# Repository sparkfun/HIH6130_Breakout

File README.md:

HIH6130 Breakout - Humidity and Temperature Sensor
===================================================

[
*HIH6130 Breakout (SEN-11295)*](https://www.sparkfun.com/products/11295)

This is a breakout for the HIH6130 digital output-type relative humidity and temperature sensor.

Repository Contents
-------------------
* **/Hardware** - All Eagle design files (.brd, .sch, .STL)
* **/Production** - Test bed files and production panel files

License Information
-------------------
The hardware is released under [Creative Commons ShareAlike 4.0 International](https://creativecommons.org/licenses/by-sa/4.0/).

Distributed as-is; no warranty is given.

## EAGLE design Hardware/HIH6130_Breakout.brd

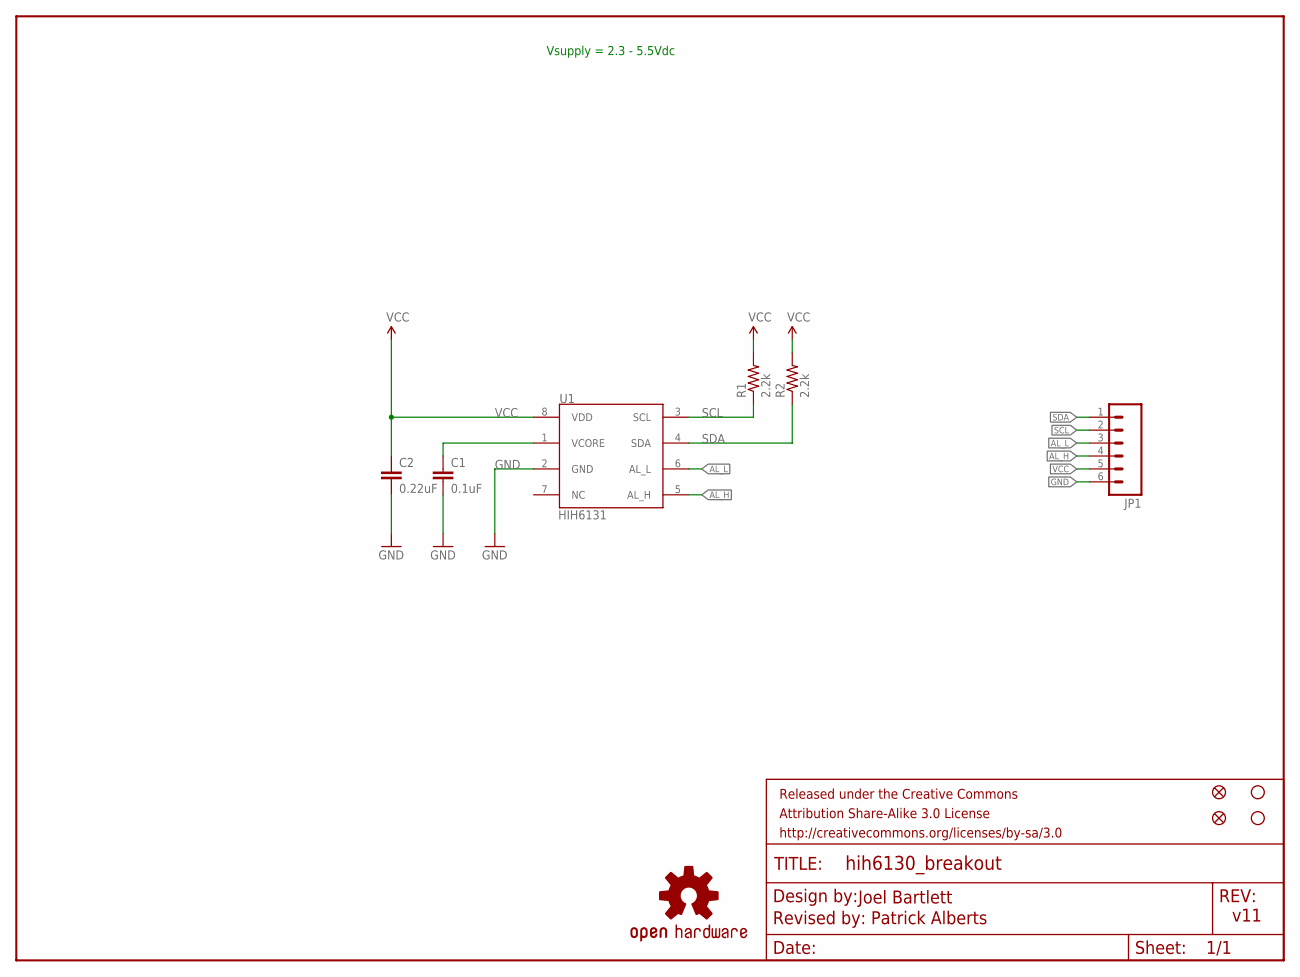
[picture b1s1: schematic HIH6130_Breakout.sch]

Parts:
C1: 0.1uF; 0603-CAP
C2: 0.22uF; 0603-CAP
FID1, FID2: FIDUCIAL1X2; FIDUCIAL-1X2
FRAME1: FRAME-LETTER; CREATIVE_COMMONS
JP1: M06SIP; 1X06
JP3, JP4: STAND-OFFTIGHT; STAND-OFF-TIGHT
R1, R2: 2.2k; 0603-RES
U1: HIH6131; SOIC8
U$2: OSHW-LOGOS; OSHW-LOGO-S

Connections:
AL_H: JP1.4, U1.5 (AL_H)
AL_L: JP1.3, U1.6 (AL_L)
GND: C1.2, C2.2, JP1.6, U1.2 (GND)
unnamed: C1.1, U1.1 (VCORE)
SCL: JP1.2, R1.1, U1.3 (SCL)
SDA: JP1.1, R2.1, U1.4 (SDA)
VCC: C2.1, JP1.5, R1.2, R2.2, U1.8 (VDD)

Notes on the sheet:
Vsupply = 2.3 - 5.5Vdc
v11
Joel Bartlett
Revised by: Patrick Alberts

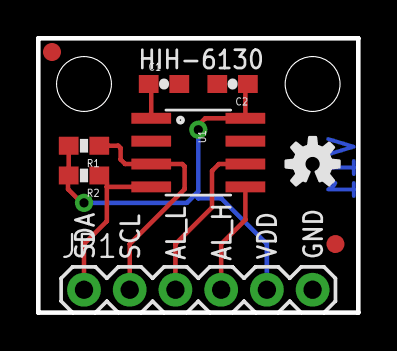
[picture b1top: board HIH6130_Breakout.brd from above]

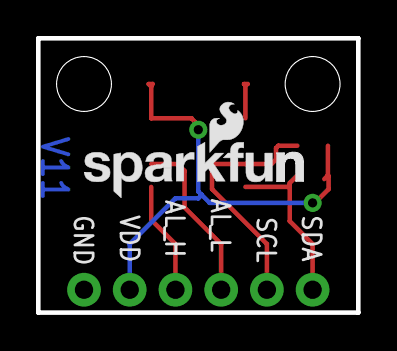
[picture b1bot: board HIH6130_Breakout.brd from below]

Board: 2 copper layers, 17.8 x 15.2 mm, 17 parts (5 on the bottom side), 7 nets.

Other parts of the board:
U$1, U$6, U$7: SFE-NEW-WEB-SOLDERMASK
U$3: SFE-LOGO-FLAME
U$8: SFE-NEW-WEB

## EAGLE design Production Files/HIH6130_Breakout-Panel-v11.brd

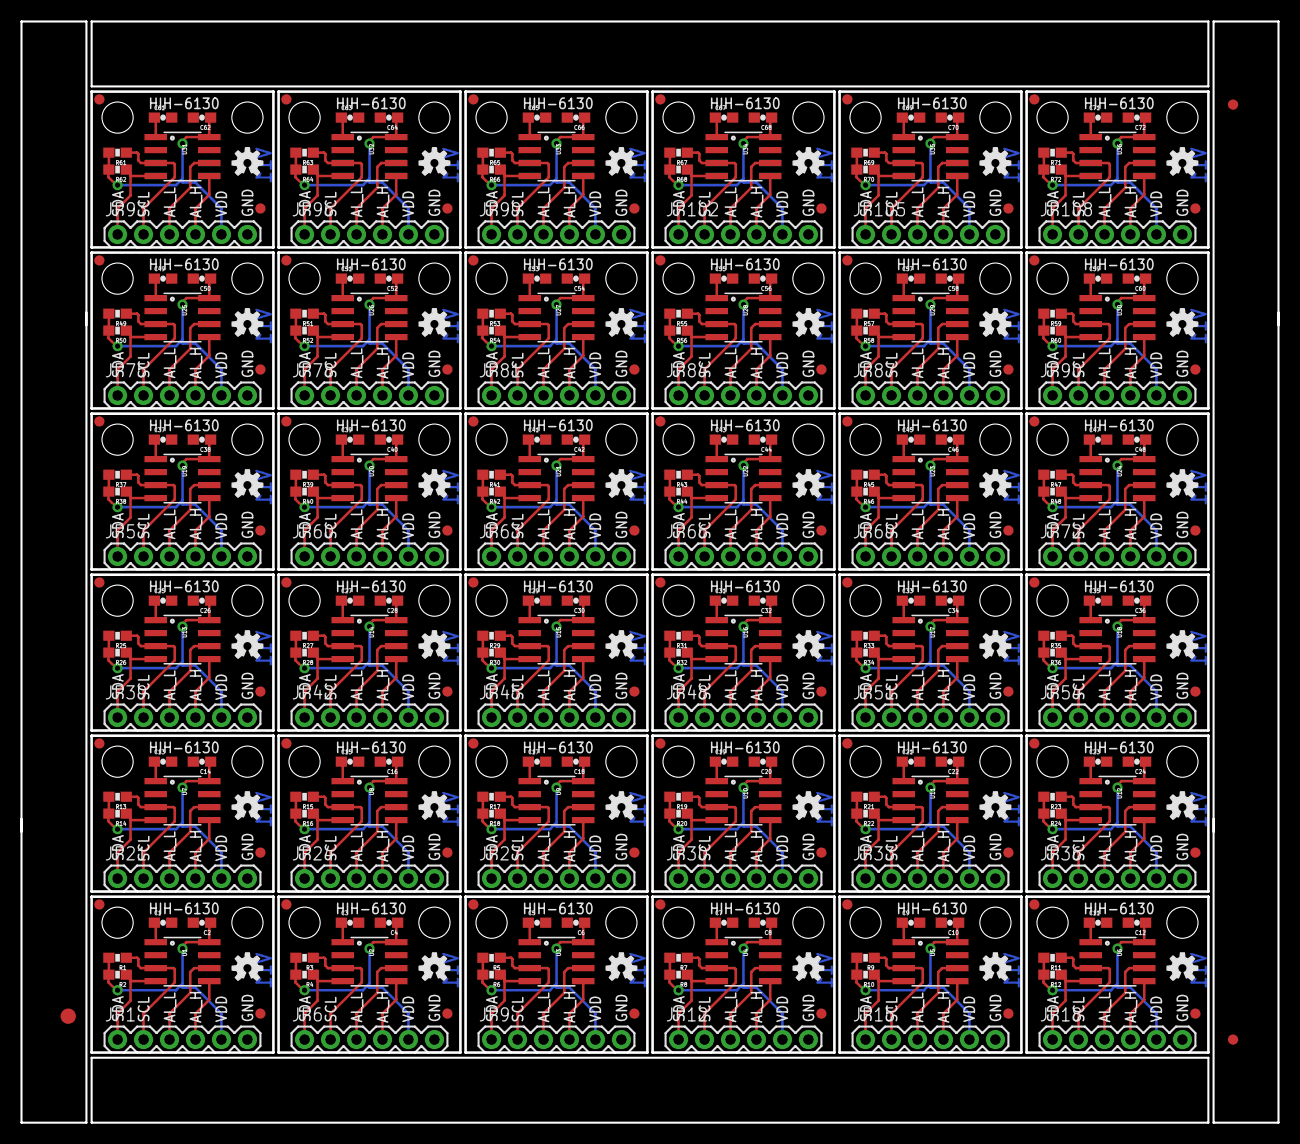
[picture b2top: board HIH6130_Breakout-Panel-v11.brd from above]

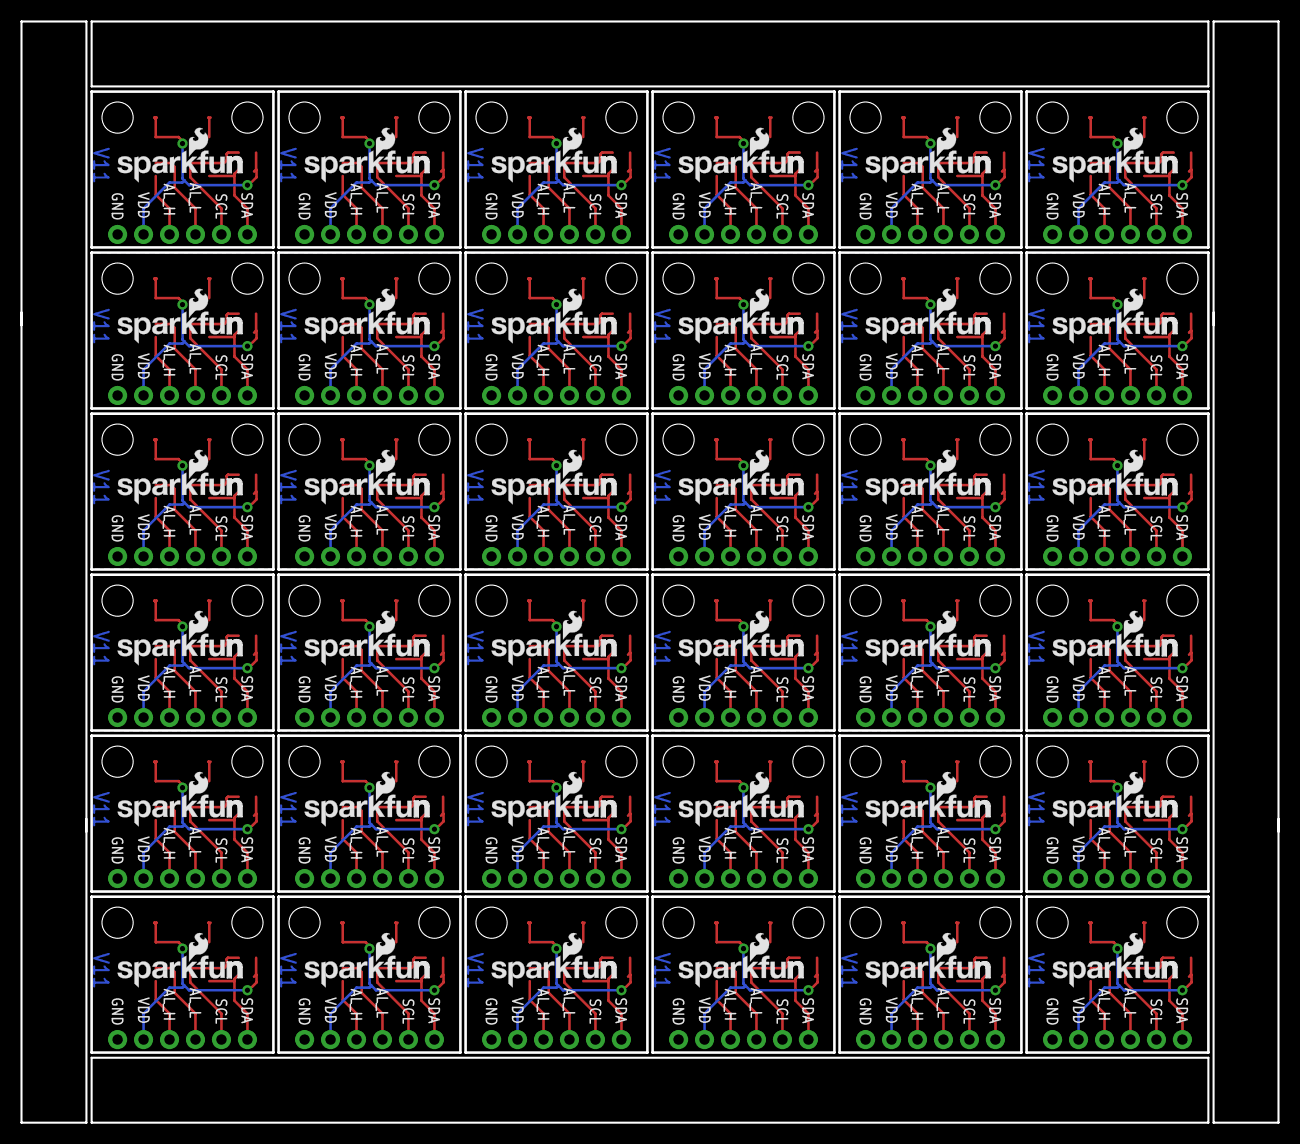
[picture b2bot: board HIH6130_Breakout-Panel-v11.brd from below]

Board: 2 copper layers, 122.9 x 107.6 mm, 579 parts (180 on the bottom side), 252 nets.

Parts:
C1, C3, C5, C7, C9, C11, C13, C15, C17, C19, C21, C23, C25, C27, C29, C31, C33, C35, C37, C39, C41, C43, C45, C47, C49, C51, C53, C55, C57, C59, C61, C63, C65, C67, C69, C71: 0.1uF; 0603-CAP
C2, C4, C6, C8, C10, C12, C14, C16, C18, C20, C22, C24, C26, C28, C30, C32, C34, C36, C38, C40, C42, C44, C46, C48, C50, C52, C54, C56, C58, C60, C62, C64, C66, C68, C70, C72: 0.22uF; 0603-CAP
E$1: FIDUCIAL-1.5X3
E$4, E$6: FIDUCIAL-1X2
FID1, FID2, FID3, FID4, FID5, FID6, FID7, FID8, FID9, FID10, FID11, FID12, FID13, FID14, FID15, FID16, FID17, FID18, FID19, FID20, FID21, FID22, FID23, FID24, FID25, FID26, FID27, FID28, FID29, FID30, FID31, FID32, FID33, FID34, FID35, FID36, FID37, FID38, FID39, FID40, FID41, FID42, FID43, FID44, FID45, FID46, FID47, FID48, FID49, FID50, FID51, FID52, FID53, FID54, FID55, FID56, FID57, FID58, FID59, FID60, FID61, FID62, FID63, FID64, FID65, FID66, FID67, FID68, FID69, FID70, FID71, FID72: FIDUCIAL1X2; FIDUCIAL-1X2
JP1, JP6, JP9, JP12, JP15, JP18, JP21, JP24, JP27, JP30, JP33, JP36, JP39, JP42, JP45, JP48, JP51, JP54, JP57, JP60, JP63, JP66, JP69, JP72, JP75, JP78, JP81, JP84, JP87, JP90, JP93, JP96, JP99, JP102, JP105, JP108: 1X06
JP2, JP3, JP4, JP5, JP7, JP8, JP10, JP11, JP13, JP14, JP16, JP17, JP19, JP20, JP22, JP23, JP25, JP26, JP28, JP29, JP31, JP32, JP34, JP35, JP37, JP38, JP40, JP41, JP43, JP44, JP46, JP47, JP49, JP50, JP52, JP53, JP55, JP56, JP58, JP59, JP61, JP62, JP64, JP65, JP67, JP68, JP70, JP71, JP73, JP74, JP76, JP77, JP79, JP80, JP82, JP83, JP85, JP86, JP88, JP89, JP91, JP92, JP94, JP95, JP97, JP98, JP100, JP101, JP103, JP104, JP106, JP107: STAND-OFFTIGHT; STAND-OFF-TIGHT
R1, R2, R3, R4, R5, R6, R7, R8, R9, R10, R11, R12, R13, R14, R15, R16, R17, R18, R19, R20, R21, R22, R23, R24, R25, R26, R27, R28, R29, R30, R31, R32, R33, R34, R35, R36, R37, R38, R39, R40, R41, R42, R43, R44, R45, R46, R47, R48, R49, R50, R51, R52, R53, R54, R55, R56, R57, R58, R59, R60, R61, R62, R63, R64, R65, R66, R67, R68, R69, R70, R71, R72: 2.2k; 0603-RES
U1, U2, U3, U4, U5, U6, U7, U8, U9, U10, U11, U12, U13, U14, U15, U16, U17, U18, U19, U20, U21, U22, U23, U24, U25, U26, U27, U28, U29, U30, U31, U32, U33, U34, U35, U36: HIH6131; SOIC8
U$1, U$5, U$6, U$7, U$10, U$11, U$14, U$16, U$17, U$20, U$22, U$23, U$26, U$28, U$29, U$32, U$34, U$35, U$38, U$40, U$41, U$44, U$46, U$47, U$50, U$52, U$53, U$56, U$58, U$59, U$62, U$64, U$65, U$68, U$70, U$71, U$74, U$76, U$77, U$80, U$82, U$83, U$86, U$88, U$89, U$92, U$94, U$95, U$98, U$100, U$101, U$104, U$106, U$107, U$110, U$112, U$113, U$116, U$118, U$119, U$122, U$124, U$125, U$128, U$130, U$131, U$134, U$136, U$137, U$140, U$142, U$143, U$146, U$148, U$149, U$152, U$154, U$155, U$158, U$160, U$161, U$164, U$166, U$167, U$170, U$172, U$173, U$176, U$178, U$179, U$182, U$184, U$185, U$188, U$190, U$191, U$194, U$196, U$197, U$200, U$202, U$203, U$206, U$208, U$209, U$212, U$214, U$215: SFE-NEW-WEB-SOLDERMASK
U$2, U$4, U$13, U$19, U$25, U$31, U$37, U$43, U$49, U$55, U$61, U$67, U$73, U$79, U$85, U$91, U$97, U$103, U$109, U$115, U$121, U$127, U$133, U$139, U$145, U$151, U$157, U$163, U$169, U$175, U$181, U$187, U$193, U$199, U$205, U$211: OSHW-LOGOS; OSHW-LOGO-S
U$3, U$9, U$15, U$21, U$27, U$33, U$39, U$45, U$51, U$57, U$63, U$69, U$75, U$81, U$87, U$93, U$99, U$105, U$111, U$117, U$123, U$129, U$135, U$141, U$147, U$153, U$159, U$165, U$171, U$177, U$183, U$189, U$195, U$201, U$207, U$213: SFE-LOGO-FLAME
U$8, U$12, U$18, U$24, U$30, U$36, U$42, U$48, U$54, U$60, U$66, U$72, U$78, U$84, U$90, U$96, U$102, U$108, U$114, U$120, U$126, U$132, U$138, U$144, U$150, U$156, U$162, U$168, U$174, U$180, U$186, U$192, U$198, U$204, U$210, U$216: SFE-NEW-WEB

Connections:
AL_H: JP1.4, U1.5
AL_H1: JP6.4, U2.5
AL_H2: JP9.4, U3.5
AL_H3: JP12.4, U4.5
AL_H4: JP15.4, U5.5
AL_H5: JP18.4, U6.5
AL_H6: JP21.4, U7.5
AL_H7: JP24.4, U8.5
AL_H8: JP27.4, U9.5
AL_H9: JP30.4, U10.5
AL_H10: JP33.4, U11.5
AL_H11: JP36.4, U12.5
AL_H12: JP39.4, U13.5
AL_H13: JP42.4, U14.5
AL_H14: JP45.4, U15.5
AL_H15: JP48.4, U16.5
AL_H16: JP51.4, U17.5
AL_H17: JP54.4, U18.5
AL_H18: JP57.4, U19.5
AL_H19: JP60.4, U20.5
AL_H20: JP63.4, U21.5
AL_H21: JP66.4, U22.5
AL_H22: JP69.4, U23.5
AL_H23: JP72.4, U24.5
AL_H24: JP75.4, U25.5
AL_H25: JP78.4, U26.5
AL_H26: JP81.4, U27.5
AL_H27: JP84.4, U28.5
AL_H28: JP87.4, U29.5
AL_H29: JP90.4, U30.5
AL_H30: JP93.4, U31.5
AL_H31: JP96.4, U32.5
AL_H32: JP99.4, U33.5
AL_H33: JP102.4, U34.5
AL_H34: JP105.4, U35.5
AL_H35: JP108.4, U36.5
AL_L: JP1.3, U1.6
AL_L1: JP6.3, U2.6
AL_L2: JP9.3, U3.6
AL_L3: JP12.3, U4.6
AL_L4: JP15.3, U5.6
AL_L5: JP18.3, U6.6
AL_L6: JP21.3, U7.6
AL_L7: JP24.3, U8.6
AL_L8: JP27.3, U9.6
AL_L9: JP30.3, U10.6
AL_L10: JP33.3, U11.6
AL_L11: JP36.3, U12.6
AL_L12: JP39.3, U13.6
AL_L13: JP42.3, U14.6
AL_L14: JP45.3, U15.6
AL_L15: JP48.3, U16.6
AL_L16: JP51.3, U17.6
AL_L17: JP54.3, U18.6
AL_L18: JP57.3, U19.6
AL_L19: JP60.3, U20.6
AL_L20: JP63.3, U21.6
AL_L21: JP66.3, U22.6
AL_L22: JP69.3, U23.6
AL_L23: JP72.3, U24.6
AL_L24: JP75.3, U25.6
AL_L25: JP78.3, U26.6
AL_L26: JP81.3, U27.6
AL_L27: JP84.3, U28.6
AL_L28: JP87.3, U29.6
AL_L29: JP90.3, U30.6
AL_L30: JP93.3, U31.6
AL_L31: JP96.3, U32.6
AL_L32: JP99.3, U33.6
AL_L33: JP102.3, U34.6
AL_L34: JP105.3, U35.6
AL_L35: JP108.3, U36.6
GND: C1.2, C2.2, JP1.6, U1.2
GND1: C3.2, C4.2, JP6.6, U2.2
GND2: C5.2, C6.2, JP9.6, U3.2
GND3: C7.2, C8.2, JP12.6, U4.2
GND4: C9.2, C10.2, JP15.6, U5.2
GND5: C11.2, C12.2, JP18.6, U6.2
GND6: C13.2, C14.2, JP21.6, U7.2
GND7: C15.2, C16.2, JP24.6, U8.2
GND8: C17.2, C18.2, JP27.6, U9.2
GND9: C19.2, C20.2, JP30.6, U10.2
GND10: C21.2, C22.2, JP33.6, U11.2
GND11: C23.2, C24.2, JP36.6, U12.2
GND12: C25.2, C26.2, JP39.6, U13.2
GND13: C27.2, C28.2, JP42.6, U14.2
GND14: C29.2, C30.2, JP45.6, U15.2
GND15: C31.2, C32.2, JP48.6, U16.2
GND16: C33.2, C34.2, JP51.6, U17.2
GND17: C35.2, C36.2, JP54.6, U18.2
GND18: C37.2, C38.2, JP57.6, U19.2
GND19: C39.2, C40.2, JP60.6, U20.2
GND20: C41.2, C42.2, JP63.6, U21.2
GND21: C43.2, C44.2, JP66.6, U22.2
GND22: C45.2, C46.2, JP69.6, U23.2
GND23: C47.2, C48.2, JP72.6, U24.2
GND24: C49.2, C50.2, JP75.6, U25.2
GND25: C51.2, C52.2, JP78.6, U26.2
GND26: C53.2, C54.2, JP81.6, U27.2
GND27: C55.2, C56.2, JP84.6, U28.2
GND28: C57.2, C58.2, JP87.6, U29.2
GND29: C59.2, C60.2, JP90.6, U30.2
GND30: C61.2, C62.2, JP93.6, U31.2
GND31: C63.2, C64.2, JP96.6, U32.2
GND32: C65.2, C66.2, JP99.6, U33.2
GND33: C67.2, C68.2, JP102.6, U34.2
GND34: C69.2, C70.2, JP105.6, U35.2
GND35: C71.2, C72.2, JP108.6, U36.2
unnamed: C1.1, U1.1
unnamed: C3.1, U2.1
unnamed: C5.1, U3.1
unnamed: C7.1, U4.1
unnamed: C9.1, U5.1
unnamed: C11.1, U6.1
unnamed: C13.1, U7.1
unnamed: C15.1, U8.1
unnamed: C17.1, U9.1
unnamed: C19.1, U10.1
unnamed: C21.1, U11.1
unnamed: C23.1, U12.1
unnamed: C25.1, U13.1
unnamed: C27.1, U14.1
unnamed: C29.1, U15.1
unnamed: C31.1, U16.1
unnamed: C33.1, U17.1
unnamed: C35.1, U18.1
unnamed: C37.1, U19.1
unnamed: C39.1, U20.1
unnamed: C41.1, U21.1
unnamed: C43.1, U22.1
unnamed: C45.1, U23.1
unnamed: C47.1, U24.1
unnamed: C49.1, U25.1
unnamed: C51.1, U26.1
unnamed: C53.1, U27.1
unnamed: C55.1, U28.1
unnamed: C57.1, U29.1
unnamed: C59.1, U30.1
unnamed: C61.1, U31.1
unnamed: C63.1, U32.1
unnamed: C65.1, U33.1
unnamed: C67.1, U34.1
unnamed: C69.1, U35.1
unnamed: C71.1, U36.1
SCL: JP1.2, R1.1, U1.3
SCL1: JP6.2, R3.1, U2.3
SCL2: JP9.2, R5.1, U3.3
SCL3: JP12.2, R7.1, U4.3
SCL4: JP15.2, R9.1, U5.3
SCL5: JP18.2, R11.1, U6.3
SCL6: JP21.2, R13.1, U7.3
SCL7: JP24.2, R15.1, U8.3
SCL8: JP27.2, R17.1, U9.3
SCL9: JP30.2, R19.1, U10.3
SCL10: JP33.2, R21.1, U11.3
SCL11: JP36.2, R23.1, U12.3
SCL12: JP39.2, R25.1, U13.3
SCL13: JP42.2, R27.1, U14.3
SCL14: JP45.2, R29.1, U15.3
SCL15: JP48.2, R31.1, U16.3
SCL16: JP51.2, R33.1, U17.3
SCL17: JP54.2, R35.1, U18.3
SCL18: JP57.2, R37.1, U19.3
SCL19: JP60.2, R39.1, U20.3
SCL20: JP63.2, R41.1, U21.3
SCL21: JP66.2, R43.1, U22.3
SCL22: JP69.2, R45.1, U23.3
SCL23: JP72.2, R47.1, U24.3
SCL24: JP75.2, R49.1, U25.3
SCL25: JP78.2, R51.1, U26.3
SCL26: JP81.2, R53.1, U27.3
SCL27: JP84.2, R55.1, U28.3
SCL28: JP87.2, R57.1, U29.3
SCL29: JP90.2, R59.1, U30.3
SCL30: JP93.2, R61.1, U31.3
SCL31: JP96.2, R63.1, U32.3
SCL32: JP99.2, R65.1, U33.3
SCL33: JP102.2, R67.1, U34.3
SCL34: JP105.2, R69.1, U35.3
SCL35: JP108.2, R71.1, U36.3
SDA: JP1.1, R2.1, U1.4
SDA1: JP6.1, R4.1, U2.4
SDA2: JP9.1, R6.1, U3.4
SDA3: JP12.1, R8.1, U4.4
SDA4: JP15.1, R10.1, U5.4
SDA5: JP18.1, R12.1, U6.4
SDA6: JP21.1, R14.1, U7.4
SDA7: JP24.1, R16.1, U8.4
SDA8: JP27.1, R18.1, U9.4
SDA9: JP30.1, R20.1, U10.4
SDA10: JP33.1, R22.1, U11.4
SDA11: JP36.1, R24.1, U12.4
SDA12: JP39.1, R26.1, U13.4
SDA13: JP42.1, R28.1, U14.4
SDA14: JP45.1, R30.1, U15.4
SDA15: JP48.1, R32.1, U16.4
SDA16: JP51.1, R34.1, U17.4
SDA17: JP54.1, R36.1, U18.4
SDA18: JP57.1, R38.1, U19.4
SDA19: JP60.1, R40.1, U20.4
SDA20: JP63.1, R42.1, U21.4
SDA21: JP66.1, R44.1, U22.4
SDA22: JP69.1, R46.1, U23.4
SDA23: JP72.1, R48.1, U24.4
SDA24: JP75.1, R50.1, U25.4
SDA25: JP78.1, R52.1, U26.4
SDA26: JP81.1, R54.1, U27.4
SDA27: JP84.1, R56.1, U28.4
SDA28: JP87.1, R58.1, U29.4
SDA29: JP90.1, R60.1, U30.4
SDA30: JP93.1, R62.1, U31.4
SDA31: JP96.1, R64.1, U32.4
SDA32: JP99.1, R66.1, U33.4
SDA33: JP102.1, R68.1, U34.4
SDA34: JP105.1, R70.1, U35.4
SDA35: JP108.1, R72.1, U36.4
VCC: C2.1, JP1.5, R1.2, R2.2, U1.8
VCC1: C4.1, JP6.5, R3.2, R4.2, U2.8
VCC2: C6.1, JP9.5, R5.2, R6.2, U3.8
VCC3: C8.1, JP12.5, R7.2, R8.2, U4.8
VCC4: C10.1, JP15.5, R9.2, R10.2, U5.8
VCC5: C12.1, JP18.5, R11.2, R12.2, U6.8
VCC6: C14.1, JP21.5, R13.2, R14.2, U7.8
VCC7: C16.1, JP24.5, R15.2, R16.2, U8.8
VCC8: C18.1, JP27.5, R17.2, R18.2, U9.8
VCC9: C20.1, JP30.5, R19.2, R20.2, U10.8
VCC10: C22.1, JP33.5, R21.2, R22.2, U11.8
VCC11: C24.1, JP36.5, R23.2, R24.2, U12.8
VCC12: C26.1, JP39.5, R25.2, R26.2, U13.8
VCC13: C28.1, JP42.5, R27.2, R28.2, U14.8
VCC14: C30.1, JP45.5, R29.2, R30.2, U15.8
VCC15: C32.1, JP48.5, R31.2, R32.2, U16.8
VCC16: C34.1, JP51.5, R33.2, R34.2, U17.8
VCC17: C36.1, JP54.5, R35.2, R36.2, U18.8
VCC18: C38.1, JP57.5, R37.2, R38.2, U19.8
VCC19: C40.1, JP60.5, R39.2, R40.2, U20.8
VCC20: C42.1, JP63.5, R41.2, R42.2, U21.8
VCC21: C44.1, JP66.5, R43.2, R44.2, U22.8
VCC22: C46.1, JP69.5, R45.2, R46.2, U23.8
VCC23: C48.1, JP72.5, R47.2, R48.2, U24.8
VCC24: C50.1, JP75.5, R49.2, R50.2, U25.8
VCC25: C52.1, JP78.5, R51.2, R52.2, U26.8
VCC26: C54.1, JP81.5, R53.2, R54.2, U27.8
VCC27: C56.1, JP84.5, R55.2, R56.2, U28.8
VCC28: C58.1, JP87.5, R57.2, R58.2, U29.8
VCC29: C60.1, JP90.5, R59.2, R60.2, U30.8
VCC30: C62.1, JP93.5, R61.2, R62.2, U31.8
VCC31: C64.1, JP96.5, R63.2, R64.2, U32.8
VCC32: C66.1, JP99.5, R65.2, R66.2, U33.8
VCC33: C68.1, JP102.5, R67.2, R68.2, U34.8
VCC34: C70.1, JP105.5, R69.2, R70.2, U35.8
VCC35: C72.1, JP108.5, R71.2, R72.2, U36.8

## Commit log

2013-12-31 Initial Commit
    brd / sch files along with git and readme
2013-12-31 0402-->0603 Schematic Update
    Converted all cap/res to 0603 footprint update schematic to "frame
    letter"
2014-01-20 SCH Cleanup
2014-01-21 Created Panel
2014-04-18 added regular fiducials
    also deleted older panel
2014-04-18 re-created panel
2014-05-01 Updating README and repo cleanup

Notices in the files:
parts and their libraries:
SparkFun-Capacitors: Licensing: CC v3.0 Share-Alike You are welcome to use this library for commercial purposes.
SparkFun-Aesthetics: Released under the Creative Commons Attribution Share-Alike 3.0 License
SparkFun-Aesthetics: http://creativecommons.org/licenses/by-sa/3.0
